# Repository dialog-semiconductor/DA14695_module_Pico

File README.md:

# Renesas DA14695MOD Pico Board

The Renesas DA14695MOD Pico board is a versatile 2-layer development board designed with compatibility and functionality in mind. Designed to be compatible with the Pico pinout, this board offers a range of features including Bluetooth Low Energy (BLE) capabilities, USB connectivity, a battery connector equipped with an on-chip charger, and 4 MB of onboard FLASH storage.

## Features

- **BLE 5.2 Connectivity**: Leverage the power of Bluetooth Low Energy 5.2 with the integrated SmartBond DA14695 SoC.
- **USB Connectivity**: Easily connect and communicate with the board using the USB interface.
- **Battery Charging**: The onboard battery connector, coupled with the on-chip charger, allows for convenient battery management.

## DA14695 Module 

The board is based on the SmartBond DA14695 Bluetooth low energy 5.2 system-on-chip (SoC), making it a comprehensive solution for various applications. The DA14695 Module encompasses all the hardware features and capabilities of the DA14695 SoC, with integrated passives, an antenna, a 32Mbit QSPI FLASH, and user-friendly software support. The module's design focuses on broad market use, offering certifications across regions. This approach translates to reduced development costs, minimized risks, and faster time-to-market.

For detailed technical specifications of the DA14695 Module, refer to the [Renesas website](https://www.renesas.com/us/en/products/wireless-connectivity/bluetooth-low-energy/da14695mod-smartbond-bluetooth-le-52-high-integration-including-usb-charger-module).

## Repository Contents

This GitHub repository houses all the design files for the DA14695MOD Pico board. These files are compatible with KiCAD 6. The full schematic is included as pdf PDF [here](Assets/Pico%20schematic%20final.pdf).

## Board Pinout

To help you get started quickly, here's a visual representation of the board's pinout:

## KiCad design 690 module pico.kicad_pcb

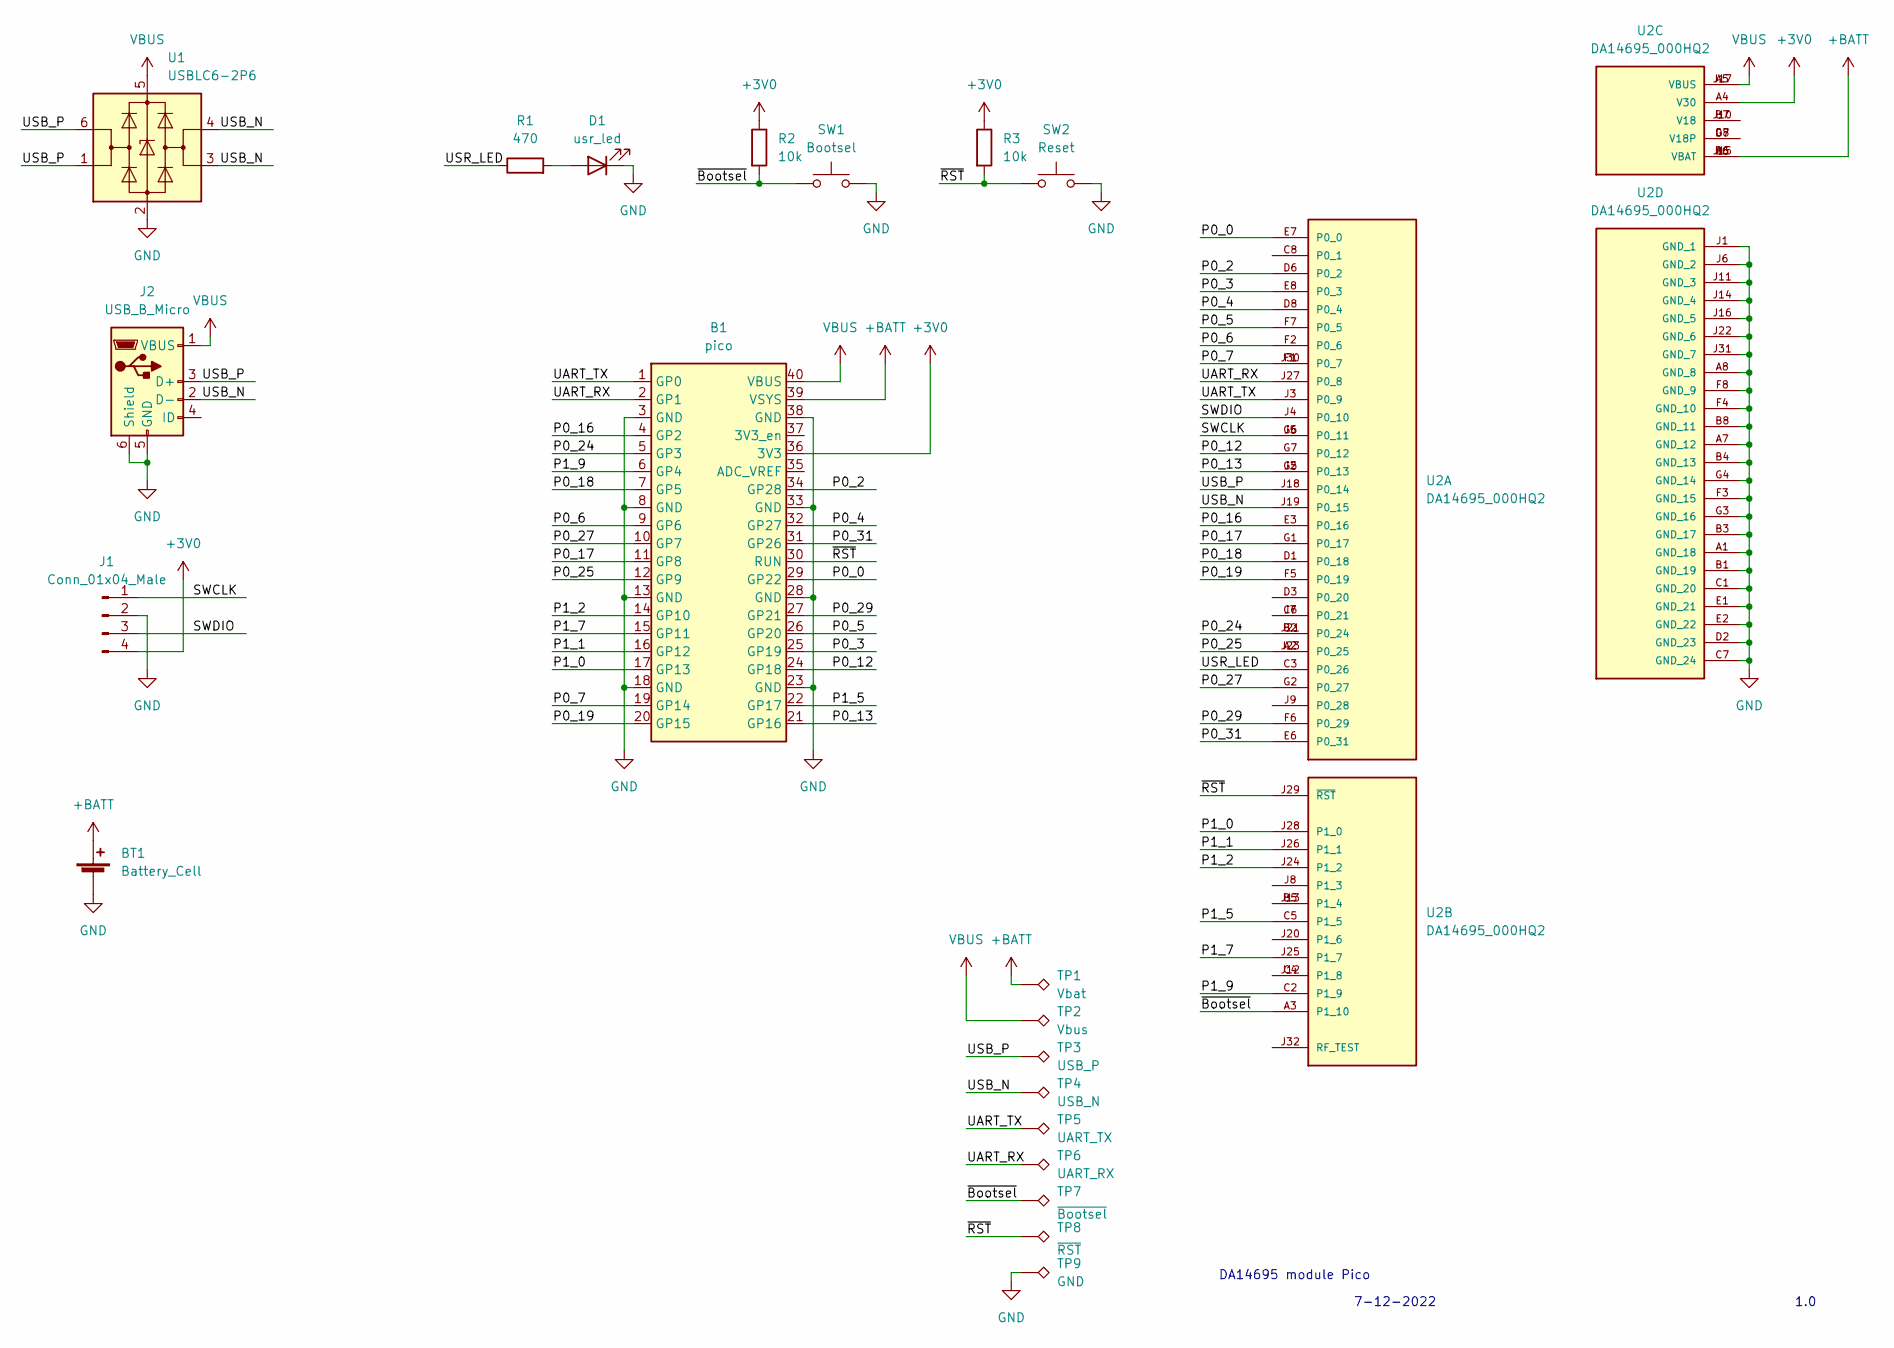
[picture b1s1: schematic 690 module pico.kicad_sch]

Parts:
B1: pico; Pico
BT1: Battery_Cell; Molex_PicoBlade_53261-0271_1x02-1MP_P1.25mm_Horizontal; LCSC partnumber C189700
D1: usr_led; LED_0603_1608Metric; LCSC partnumber C72043
J1: Conn_01x04_Male; PinHeader_1x04_P2.54mm_Vertical
J2: USB_B_Micro; USB_Micro-B_Amphenol_10118194_Horizontal; LCSC partnumber C381144
R1: 470; R_0603_1608Metric; LCSC partnumber C23179
R2, R3: 10k; R_0603_1608Metric; LCSC partnumber C25804
SW1: Bootsel; SW_SPST_B3U-1000P; LCSC partnumber C231329
SW2: Reset; SW_SPST_B3U-1000P; LCSC partnumber C231329
TP1: Vbat; TestPoint_Pad_1.0x1.0mm_custom
TP2: Vbus; TestPoint_Pad_1.0x1.0mm_custom
TP3: USB_P; TestPoint_Pad_1.0x1.0mm_custom
TP4: USB_N; TestPoint_Pad_1.0x1.0mm_custom
TP5: UART_TX; TestPoint_Pad_1.0x1.0mm_custom
TP6: UART_RX; TestPoint_Pad_1.0x1.0mm_custom
TP7: ~{Bootsel}; TestPoint_Pad_1.0x1.0mm_custom
TP8: ~{RST}; TestPoint_Pad_1.0x1.0mm_custom
TP9: GND; TestPoint_Pad_1.0x1.0mm_custom
U1: USBLC6-2P6; SOT-666; LCSC partnumber C2827693
U2: DA14695_000HQ2; MODULE_DA14695_000HQ2

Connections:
+3V0: B1.36 (3V3), J1.4, R2.1, R3.1, U2.A4 (V30)
+BATT: B1.39 (VSYS), BT1.2 (+), TP1.1, U2.A6 (VBAT), U2.B6 (VBAT), U2.J15 (VBAT)
/P0_0: B1.29 (GP22), U2.E7 (P0_0)
/P0_2: B1.34 (GP28), U2.D6 (P0_2)
/P0_3: B1.25 (GP19), U2.E8 (P0_3)
/P0_4: B1.32 (GP27), U2.D8 (P0_4)
/P0_5: B1.26 (GP20), U2.F7 (P0_5)
/P0_6: B1.9 (GP6), U2.F2 (P0_6)
/P0_7: B1.19 (GP14), U2.F1 (P0_7), U2.J30 (P0_7)
/P0_12: B1.24 (GP18), U2.G7 (P0_12)
/P0_13: B1.21 (GP16), U2.G5 (P0_13), U2.J2 (P0_13)
/P0_16: B1.4 (GP2), U2.E3 (P0_16)
/P0_17: B1.11 (GP8), U2.G1 (P0_17)
/P0_18: B1.7 (GP5), U2.D1 (P0_18)
/P0_19: B1.20 (GP15), U2.F5 (P0_19)
/P0_24: B1.5 (GP3), U2.B2 (P0_24), U2.J21 (P0_24)
/P0_25: B1.12 (GP9), U2.A2 (P0_25), U2.J23 (P0_25)
/P0_27: B1.10 (GP7), U2.G2 (P0_27)
/P0_29: B1.27 (GP21), U2.F6 (P0_29)
/P0_31: B1.31 (GP26), U2.E6 (P0_31)
/P1_0: B1.17 (GP13), U2.J28 (P1_0)
/P1_1: B1.16 (GP12), U2.J26 (P1_1)
/P1_2: B1.14 (GP10), U2.J24 (P1_2)
/P1_5: B1.22 (GP17), U2.C5 (P1_5)
/P1_7: B1.15 (GP11), U2.J25 (P1_7)
/P1_9: B1.6 (GP4), U2.C2 (P1_9)
/SWCLK: J1.1, U2.G6 (P0_11), U2.J5 (P0_11)
/SWDIO: J1.3, U2.J4 (P0_10)
/UART_RX: B1.2 (GP1), TP6.1, U2.J27 (P0_8)
/UART_TX: B1.1 (GP0), TP5.1, U2.J3 (P0_9)
/USB_N: J2.2 (D-), TP4.1, U1.3 (I/O2), U1.4 (I/O2), U2.J19 (P0_15)
/USB_P: J2.3 (D+), TP3.1, U1.1 (I/O1), U1.6 (I/O1), U2.J18 (P0_14)
/USR_LED: R1.1, U2.C3 (P0_26)
/~Bootsel: R2.2, SW1.1, TP7.1, U2.A3 (P1_10)
/~RST: B1.30 (RUN), R3.2, SW2.1, TP8.1, U2.J29 (~RST)
GND: B1.3 (GND), B1.8 (GND), B1.13 (GND), B1.18 (GND), B1.23 (GND), B1.28 (GND), B1.33 (GND), B1.38 (GND), BT1.1 (-), D1.1 (K), J1.2, J2.5 (GND), J2.6 (Shield), SW1.2, SW2.2, TP9.1, U1.2 (GND), U2.A1 (GND_18), U2.A7 (GND_12), U2.A8 (GND_8), U2.B1 (GND_19), U2.B3 (GND_17), U2.B4 (GND_13), U2.B8 (GND_11), U2.C1 (GND_20), U2.C7 (GND_24), U2.D2 (GND_23), U2.E1 (GND_21), U2.E2 (GND_22), U2.F3 (GND_15), U2.F4 (GND_10), U2.F8 (GND_9), U2.G3 (GND_16), U2.G4 (GND_14), U2.J1 (GND_1), U2.J6 (GND_2), U2.J11 (GND_3), U2.J14 (GND_4), U2.J16 (GND_5), U2.J22 (GND_6), U2.J31 (GND_7)
unnamed: D1.2 (A), R1.2
unnamed: U2.B5 (P1_4), U2.J13 (P1_4)
unnamed: U2.B7 (V18), U2.J10 (V18)
unnamed: U2.C4 (P1_8), U2.J12 (P1_8)
unnamed: U2.C6 (P0_21), U2.J7 (P0_21)
unnamed: U2.D7 (V18P), U2.G8 (V18P)
VBUS: B1.40 (VBUS), J2.1 (VBUS), TP2.1, U1.5 (VBUS), U2.A5 (VBUS), U2.J17 (VBUS)

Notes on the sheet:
1.0
DA14695 module Pico
7-12-2022

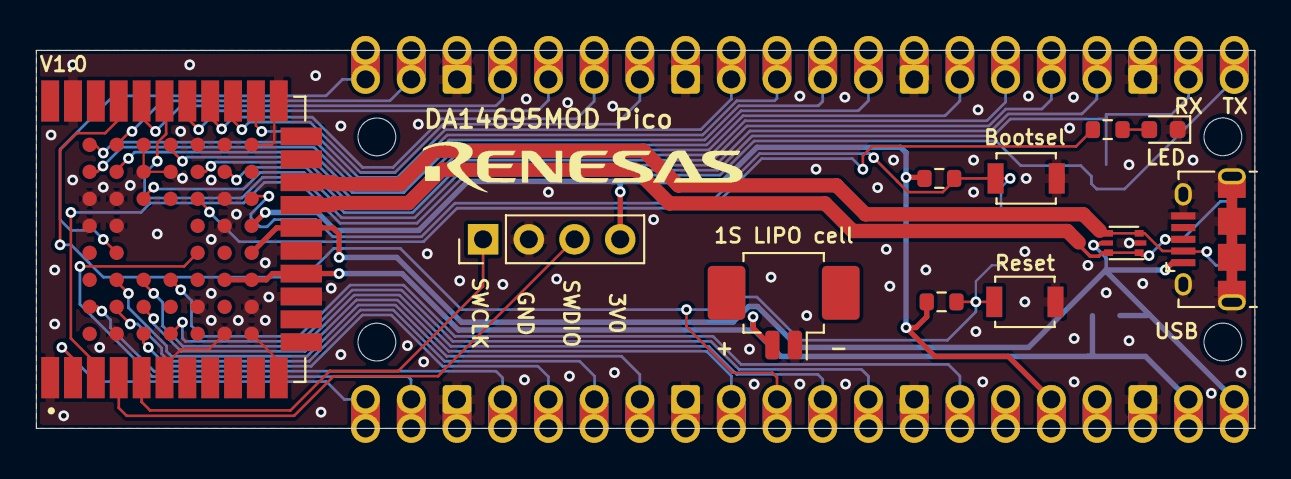
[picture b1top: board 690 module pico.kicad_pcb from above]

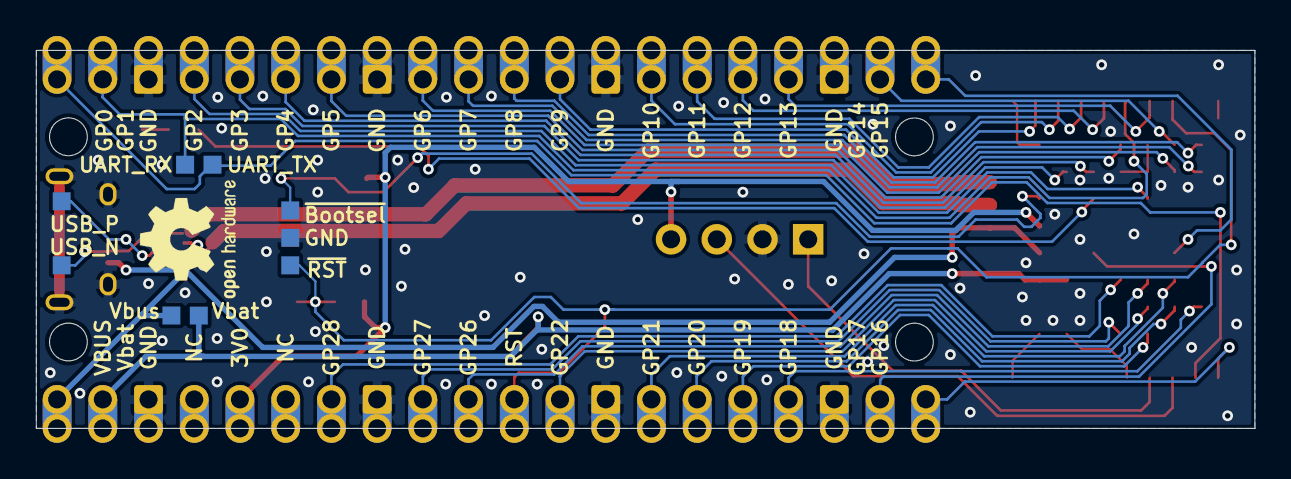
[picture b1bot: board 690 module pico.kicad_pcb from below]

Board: 2 copper layers, 67.7 x 21.0 mm, 21 parts (9 on the bottom side), 43 nets.

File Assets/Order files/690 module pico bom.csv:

Component,Description,Part,References,Value,Footprint,Quantity Per PCB,Datasheet,LCSC partnumber,MANUFACTURER,SNAPEDA_PN,STANDARD
1,Single-cell battery,Battery_Cell,BT1,Battery_Cell,Molex_PicoBlade_53261-0271_1x02-1MP_P1.25mm_Horizontal,1,~,C189700,,,
2,Light emitting diode,LED,D1,usr_led,LED_0603_1608Metric,1,~,C72043,,,
3,"Generic connector, single row, 01x04, script generated (kicad-library-utils/schlib/autogen/connector/)",Conn_01x04_Male,J1,Conn_01x04_Male,PinHeader_1x04_P2.54mm_Vertical,1,~,,,,
4,USB Micro Type B connector,USB_B_Micro,J2,USB_B_Micro,USB_Micro-B_Amphenol_10118194_Horizontal,1,~,C404969,,,
5,Resistor,R,R1,470,R_0603_1608Metric,1,~,C23179,,,
6,Resistor,R,R2 R3,10k,R_0603_1608Metric,2,~,C25804,,,
7,"Push button switch, generic, two pins",SW_Push,SW1,Bootsel,SW_SPST_B3U-1000P,1,~,C231329,,,
8,"Push button switch, generic, two pins",SW_Push,SW2,Reset,SW_SPST_B3U-1000P,1,~,C231329,,,
9,,DA14695_000HQ2,U2,DA14695_000HQ2,MODULE_DA14695_000HQ2,1,,,Renesas,DA14695_HQ2_Module,Manufacturer Recommendations
10,"Very low capacitance ESD protection diode, 2 data-line, SOT-666",USBLC6-2P6,U1,USBLC6-2P6,SOT-666,1,https://www.st.com/resource/en/datasheet/usblc6-2.pdf,C2827693,,,

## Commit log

2022-12-08 Ordered version 1
2022-12-12 Added pinout picture
2022-12-13 add brief readme
2023-01-20 Add order files and replace USB connector
2023-08-10 Readme rewrite
